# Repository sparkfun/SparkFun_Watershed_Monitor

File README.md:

# SparkFun Watershed Monitor

Repository Contents
-------------------

* **/Documentation** - Data sheets, additional product information
* **/Hardware** - Eagle design files (.brd, .sch)
* **/Production** - Production panel files (.brd)

License Information
-------------------

This product is _**open source**_! 

Please review the LICENSE.md file for license information. 

If you have any questions or concerns on licensing, please contact technical support on our [SparkFun forums](https://forum.sparkfun.com/viewforum.php?f=152).

Distributed as-is; no warranty is given.

- Your friends at SparkFun.

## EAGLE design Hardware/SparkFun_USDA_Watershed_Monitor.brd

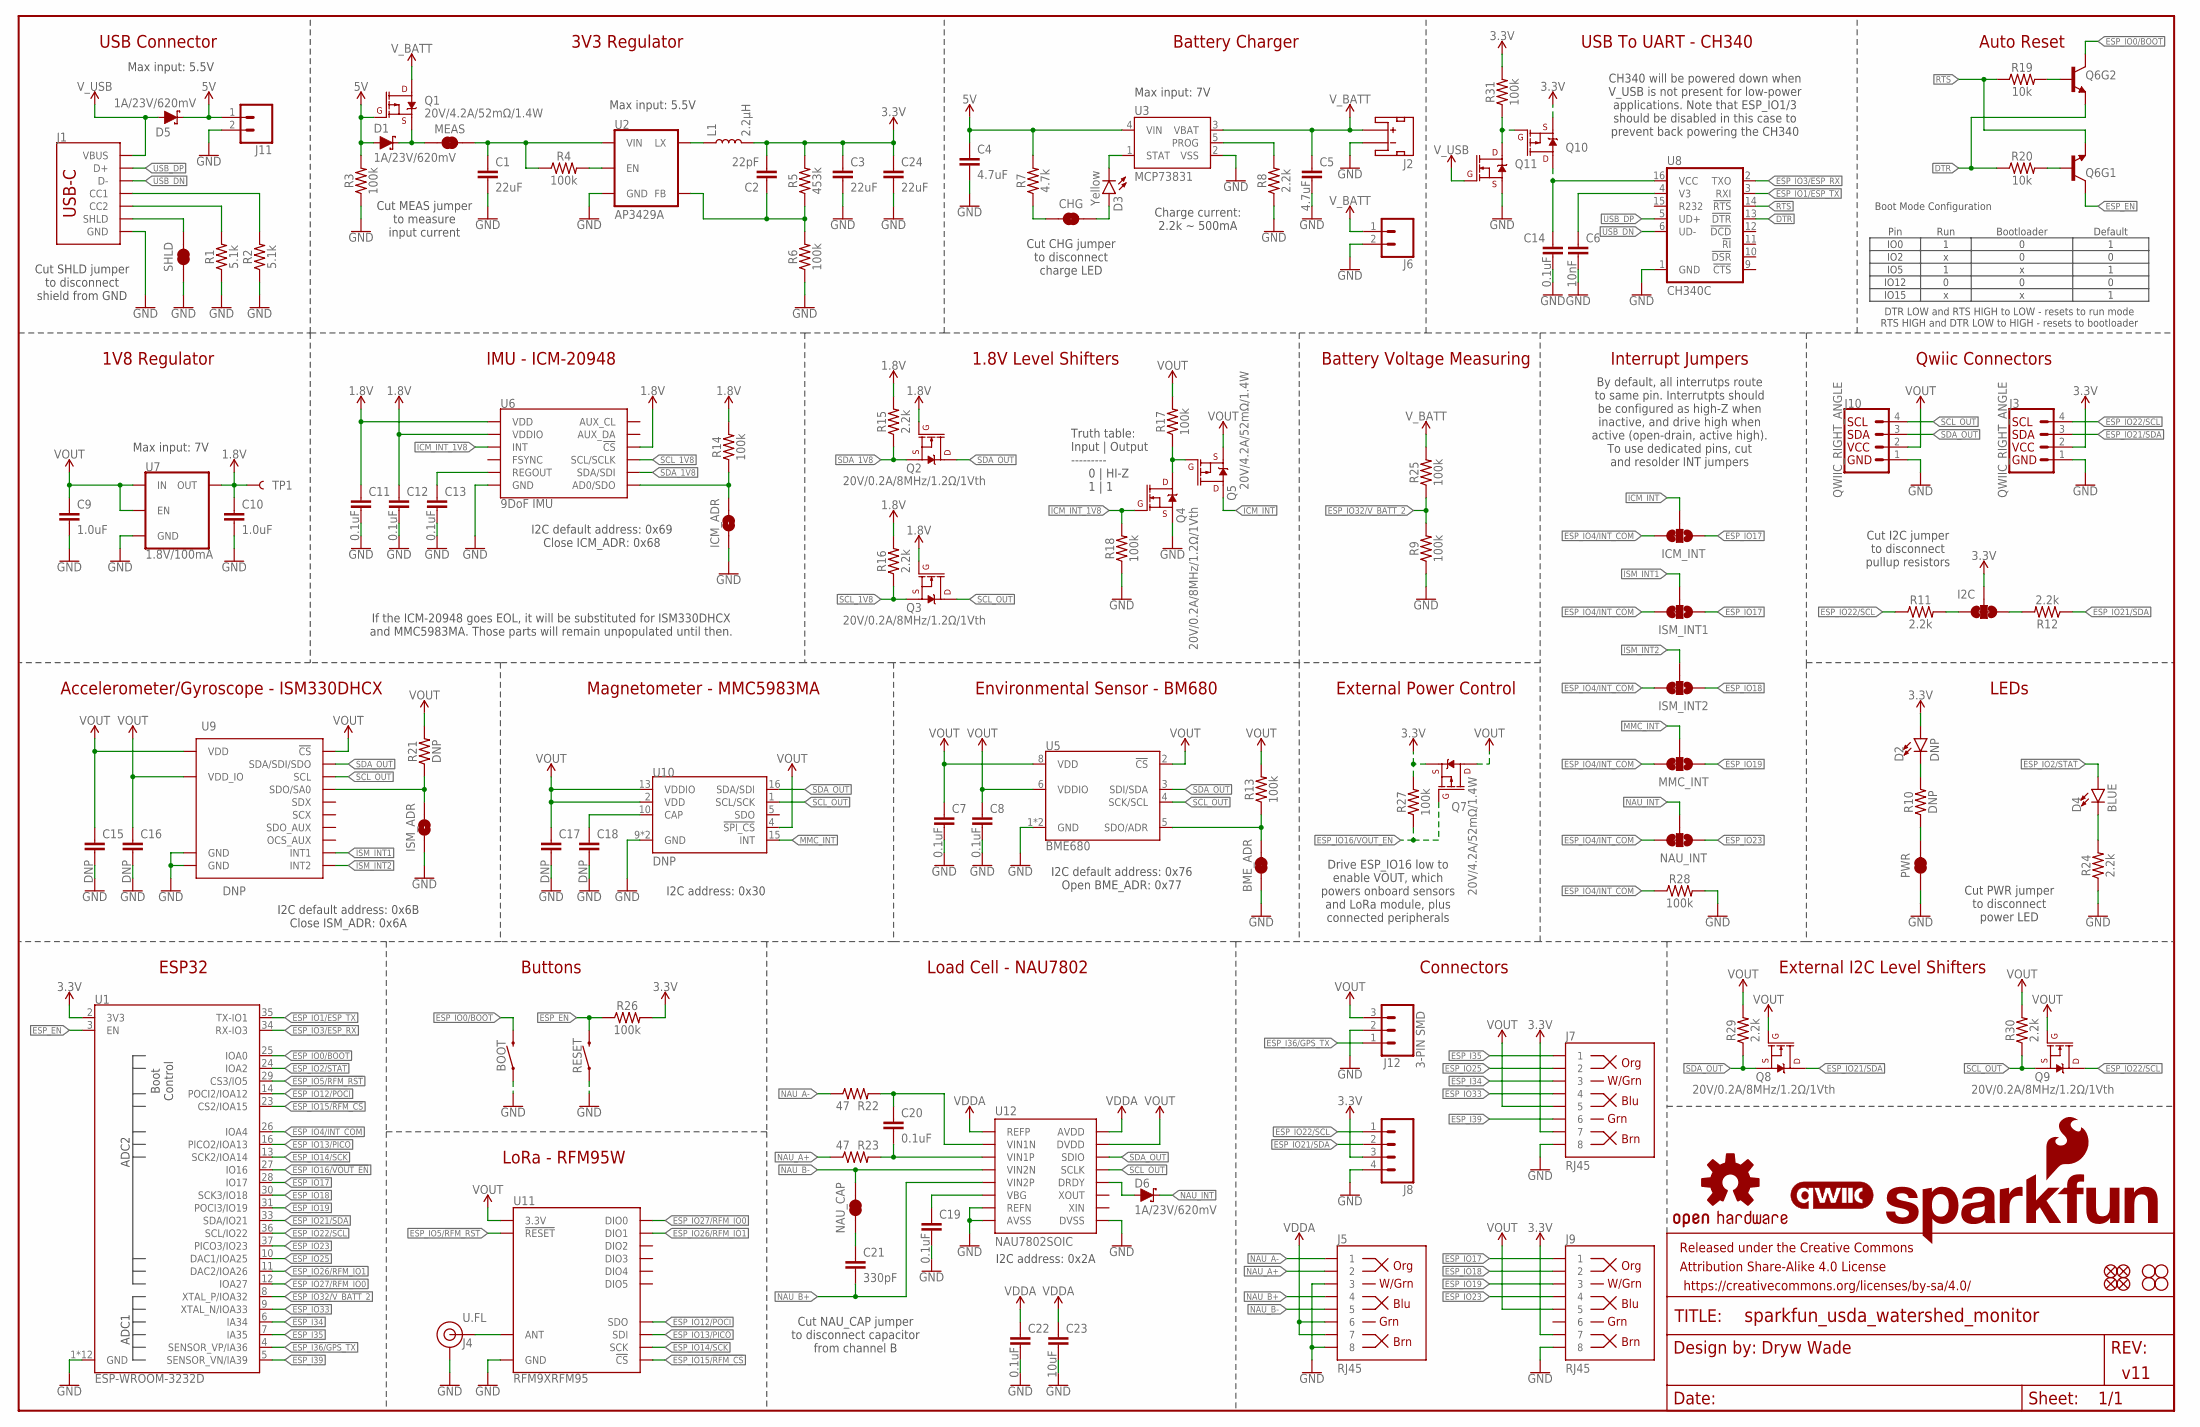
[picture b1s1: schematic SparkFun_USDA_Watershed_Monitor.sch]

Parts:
BME_ADR: JUMPER-SMT_2_NC_TRACE_SILK; SMT-JUMPER_2_NC_TRACE_SILK
BOOT: MOMENTARY-SWITCH-SPST-SMD-4.6X2.8MM; TACTILE_SWITCH_SMD_4.6X2.8MM
C1, C3, C24: 22uF; 0805
C2: 22pF; 0603
C4, C5: 4.7uF; 0603
C6: 10nF; 0603
C7, C8, C11, C12, C13, C14, C19, C20, C22: 0.1uF; 0603
C9, C10: 1.0uF; 0603
C15, C16, C17, C18: DNP; 0603
C21: 330pF; 0603
C23: 10uF; 0603
CHG: JUMPER-SMT_2_NC_TRACE_SILK; SMT-JUMPER_2_NC_TRACE_SILK
D1, D5, D6: 1A/23V/620mV; SOD-323
D2: DNP; LED-0603
D3: Yellow; LED-0603
D4: BLUE; LED-0603
FD1, FD2, FD3, FD4: FIDUCIAL1X2; FIDUCIAL-1X2
FRAME1: FRAME-LEDGER; CREATIVE_COMMONS
H1, H2, H3, H4: STAND-OFF
I2C: JUMPER-SMT_3_2-NC_TRACE_SILK; SMT-JUMPER_3_2-NC_TRACE_SILK
ICM_ADR: JUMPER-SMT_2_NO_SILK; SMT-JUMPER_2_NO_SILK
ICM_INT: JUMPER-SMT_3_1-NC_TRACE_SILK; SMT-JUMPER_3_1-NC_TRACE_SILK
ISM_ADR: JUMPER-SMT_2_NO_SILK; SMT-JUMPER_2_NO_SILK
ISM_INT1, ISM_INT2: JUMPER-SMT_3_1-NC_TRACE_SILK; SMT-JUMPER_3_1-NC_TRACE_SILK
J1: USB_C_2-LAYER_PADS; USB-C-16P-2LAYER-PADS
J2: JST_2MM_MALE; JST-2-SMD
J3, J10: QWIIC_RIGHT_ANGLE; JST04_1MM_RA
J4: U.FL
J5, J7, J9: RJ45; RJ45-8
J6, J11: CONN_021X02_NO_SILK; 1X02_NO_SILK
J8: CONN_041X04_NO_SILK_NO_POP; 1X04_NO_SILK
J12: 3-PIN SMD; JST-3-SMD
L1: 2.2μH; INDUCTOR_4X4MM
LOGO1: SFE_LOGO_NAME_FLAME.1_INCH; SFE_LOGO_NAME_FLAME_.1
LOGO2: OSHW-LOGOS; OSHW-LOGO-S
LOGO3: QWIIC_LOGO_4MM; QWIIC_4MM
MEAS: JUMPER-COMBO_2_NC_TRACE; COMBO-JUMPER_2_NC_TRACE
MMC_INT: JUMPER-SMT_3_1-NC_TRACE_SILK; SMT-JUMPER_3_1-NC_TRACE_SILK
NAU_CAP: JUMPER-SMT_2_NC_TRACE_SILK; SMT-JUMPER_2_NC_TRACE_SILK
NAU_INT: JUMPER-SMT_3_1-NC_TRACE_SILK; SMT-JUMPER_3_1-NC_TRACE_SILK
PWR: JUMPER-SMT_2_NC_TRACE_SILK; SMT-JUMPER_2_NC_TRACE_SILK
Q1, Q5, Q7, Q10: 20V/4.2A/52mΩ/1.4W; SOT23-3
Q2, Q3, Q4, Q8, Q9, Q11: 20V/0.2A/8MHz/1.2Ω/1Vth; SOT-416FL
Q6: TRANS_NPN_DUAL-MBT3904DW1T1; SC70-6
R1, R2: 5.1k; 0603
R3, R4, R6, R9, R13, R14, R17, R18, R25, R26, R27, R28, R31: 100k; 0603
R5: 453k; 0603
R7: 4.7k; 0603
R8, R11, R12, R15, R16, R24, R29, R30: 2.2k; 0603
R10, R21: DNP; 0603
R19, R20: 10k; 0603
R22, R23: 47; 0603
RESET: MOMENTARY-SWITCH-SPST-SMD-4.6X2.8MM; TACTILE_SWITCH_SMD_4.6X2.8MM
SHLD: JUMPER-SMT_2_NC_TRACE_SILK; SMT-JUMPER_2_NC_TRACE_SILK
TP1: TEST-POINT3X4; PAD.03X.04
U1: ESP-WROOM-3232D; ESP-WROOM-32D
U2: AP3429A; SOT23-5
U3: MCP73831; SOT23-5
U5: BME680; LGA3.0X3.0
U6: 9DoF IMU; QFN24-3X3-ICM-20948
U7: 1.8V/100mA; SC70
U8: CH340C; SO016
U9: DNP; LGA-14L
U10: DNP; LGA-16-3X3MM-4X4PINS
U11: RFM9XRFM95; RFM95
U12: NAU7802SOIC; SO16

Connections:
1.8V: C10.1, C11.1, C12.1, Q2.1 (G), Q3.1 (G), R14.2, R15.2, R16.2, TP1.1, U6.8 (VDDIO), U6.13 (VDD), U6.22 (!CS), U7.5 (OUT)
3.3V: C2.2, C3.1, C24.1, D2.A, I2C.2, J3.2, J7.7, J8.3, J9.7, L1.P$2 (2), Q7.2 (S), Q10.2 (S), R5.2, R26.2, R27.2, R31.2, U1.2 (3V3)
3V3_EN: R4.2, U2.1 (EN)
5V: C4.1, D1.A, D5.C, J11.1, Q1.1 (G), R3.2, R7.2, U3.4 (VIN)
DTR: Q6.1 (E), R20.1, U8.13 (!DTR)
ESP_EN: Q6.3 (C), R26.1, RESET.3 (2), RESET.4 (2), U1.3 (EN)
ESP_I34: J7.3, U1.6 (IA34)
ESP_I35: J7.1, U1.7 (IA35)
ESP_I36/GPS_TX: J12.1 (3), U1.4 (SENSOR_VP/IA36)
ESP_I39: J7.6, U1.5 (SENSOR_VN/IA39)
ESP_IO0/BOOT: BOOT.3 (2), BOOT.4 (2), Q6.6 (C), U1.25 (IOA0)
ESP_IO1/ESP_TX: U1.35 (TX-IO1), U8.3 (RXI)
ESP_IO2/STAT: D4.A, U1.24 (IOA2)
ESP_IO3/ESP_RX: U1.34 (RX-IO3), U8.2 (TXO)
ESP_IO4/INT_COM: ICM_INT.3, ISM_INT1.3, ISM_INT2.3, MMC_INT.3, NAU_INT.3, R28.1, U1.26 (IOA4)
ESP_IO5/!RFM_RST!: U1.29 (CS3/IO5), U11.!RESET
ESP_IO12/POCI: U1.14 (POCI2/IOA12), U11.SDO
ESP_IO13/PICO: U1.16 (PICO2/IOA13), U11.SDI
ESP_IO14/SCK: U1.13 (SCK2/IOA14), U11.SCK
ESP_IO15/!RFM_CS!: U1.23 (CS2/IOA15), U11.NSS (!CS!)
ESP_IO16/!VOUT_EN!: Q7.1 (G), R27.1, U1.27 (IO16)
ESP_IO17: ICM_INT.1, ISM_INT1.1, J9.1, U1.28 (IO17)
ESP_IO18: ISM_INT2.1, J9.2, U1.30 (SCK3/IO18)
ESP_IO19: J9.3, MMC_INT.1, U1.31 (POCI3/IO19)
ESP_IO21/SDA: J3.3, J8.2, Q8.3 (D), R12.1, U1.33 (SDA/IO21)
ESP_IO22/SCL: J3.4, J8.1, Q9.3 (D), R11.1, U1.36 (SCL/IO22)
ESP_IO23: J9.4, NAU_INT.1, U1.37 (PICO3/IO23)
ESP_IO25: J7.2, U1.10 (DAC1/IOA25)
ESP_IO26/RFM_IO1: U1.11 (DAC2/IOA26), U11.DIO1
ESP_IO27/RFM_IO0: U1.12 (IOA27), U11.DIO0
ESP_IO32/V_BATT_2: R9.2, R25.1, U1.8 (XTAL_P/IOA32)
ESP_IO33: J7.4, U1.9 (XTAL_N/IOA33)
GND: BME_ADR.1, BOOT.1, BOOT.2 (1), C1.2, C3.2, C4.2, C5.2, C6.2, C7.2, C8.2, C9.2, C10.2, C11.2, C12.2, C13.2, C14.2, C15.2, C16.2, C17.2, C18.2, C19.2, C22.2, C23.2, C24.2, ICM_ADR.1, ISM_ADR.1, J1.GND, J1.GND2 (GND), J2.1 (-), J3.1, J4.1 (GND), J4.2 (GND), J5.3, J5.8, J6.2, J7.8, J8.4, J9.8, J10.1, J11.2, J12.2, PWR.1, Q4.2 (S), Q11.2 (S), R1.1, R2.1, R3.1, R6.1, R8.1, R9.1, R18.1, R24.1, R28.2, RESET.1, RESET.2 (1), SHLD.1, U1.1 (GND), U1.15 (GND), U1.38 (GND), U1.GND, U1.GNDT1 (GND), U1.GNDT2 (GND), U1.GNDT3 (GND), U1.GNDT4 (GND), U1.GNDT5 (GND), U1.GNDT6 (GND), U1.GNDT7 (GND), U1.GNDT8 (GND), U2.2 (GND), U3.2 (VSS), U5.1 (GND), U5.7 (GND), U6.18 (GND), U6.20 (GND), U7.2 (GND), U8.1 (GND), U9.P6 (GND), U9.P7 (GND), U10.9 (GND), U10.11 (GND), U11.GND@1 (GND), U11.GND@2 (GND), U11.GND@3 (GND), U12.7 (REFN), U12.8 (AVSS), U12.9 (DVSS)
ICM_INT: ICM_INT.2, Q5.3 (D)
ICM_INT_1V8: Q4.1 (G), R18.2, U6.12 (INT)
ISM_INT1: ISM_INT1.2, U9.P4 (INT1)
ISM_INT2: ISM_INT2.2, U9.P9 (INT2)
MMC_INT: MMC_INT.2, U10.15 (INT)
unnamed: D4.C, R24.2
unnamed: L1.P$1 (1), U2.3 (LX)
unnamed: C1.1, MEAS.2, MEAS.4 (2), R4.1, U2.4 (VIN)
unnamed: J1.B5 (CC2), R1.2
unnamed: J1.A5 (CC1), R2.2
unnamed: D1.C, MEAS.1, MEAS.3 (1), Q1.2 (S)
unnamed: C2.1, R5.1, R6.2, U2.5 (FB)
unnamed: D3.C, U3.1 (STAT)
unnamed: CHG.2, D3.A
unnamed: CHG.1, R7.1
unnamed: R8.2, U3.5 (PROG)
unnamed: C6.1, U8.4 (V3)
unnamed: BME_ADR.2, R13.1, U5.5 (SDO/ADR)
unnamed: C13.1, U6.10 (REGOUT)
unnamed: I2C.1, R12.2
unnamed: I2C.3, R11.2
unnamed: ICM_ADR.2, R14.1, U6.9 (AD0/SDO)
unnamed: Q6.5 (B), R20.2
unnamed: Q6.2 (B), R19.2
unnamed: C18.1, U10.10 (CAP)
unnamed: ISM_ADR.2, R21.1, U9.P1 (SDO/SA0)
unnamed: C19.1, U12.6 (VBG)
unnamed: D2.C, R10.2
unnamed: C21.1, NAU_CAP.1
unnamed: J4.FEED (SIGNAL), U11.ANT
unnamed: PWR.2, R10.1
unnamed: C20.2, R23.2, U12.3 (VIN1P)
unnamed: C20.1, R22.2, U12.2 (VIN1N)
unnamed: D6.A, U12.12 (DRDY)
unnamed: Q4.3 (D), Q5.1 (G), R17.1
unnamed: Q10.1 (G), Q11.3 (D), R31.1
unnamed: C14.1, Q10.3 (D), U8.16 (VCC)
NAU_A+: J5.2, R23.1
NAU_A-: J5.1, R22.1
NAU_B+: C21.2, J5.4, U12.5 (VIN2P)
NAU_B-: J5.5, NAU_CAP.2, U12.4 (VIN2N)
NAU_INT: D6.C, NAU_INT.2
RTS: Q6.4 (E), R19.1, U8.14 (!RTS)
SCL_1V8: Q3.2 (S), R16.1, U6.23 (SCL/SCLK)
SCL_OUT: J10.4, Q3.3 (D), Q9.2 (S), R30.1, U5.4 (SCK/SCL), U9.P13 (SCL), U10.1 (SCL/SCK), U12.13 (SCLK)
SDA_1V8: Q2.2 (S), R15.1, U6.24 (SDA/SDI)
SDA_OUT: J10.3, Q2.3 (D), Q8.2 (S), R29.1, U5.3 (SDI/SDA), U9.P14 (SDA/SDI/SDO), U10.16 (SDA/SDI), U12.14 (SDIO)
SHLD: J1.SHLD1 (SHLD), J1.SHLD2 (SHLD), J1.SHLD3 (SHLD), J1.SHLD4 (SHLD), SHLD.2
USB_DN: J1.A7 (D-), J1.B7 (D-), U8.6 (UD-)
USB_DP: J1.A6 (D+), J1.B6 (D+), U8.5 (UD+)
VDDA: C22.1, C23.1, J5.6, J5.7, U12.1 (REFP), U12.16 (AVDD)
VOUT: C7.1, C8.1, C9.1, C15.1, C16.1, C17.1, J7.5, J9.5, J10.2, J12.3 (1), Q5.2 (S), Q7.3 (D), Q8.1 (G), Q9.1 (G), R13.2, R17.2, R21.2, R29.2, R30.2, U5.2 (!CS), U5.6 (VDDIO), U5.8 (VDD), U7.1 (IN), U7.3 (EN), U9.P5 (VDD_IO), U9.P8 (VDD), U9.P12 (!CS!), U10.2 (VDD), U10.4 (!SPI_CS!), U10.13 (VDDIO), U11.3.3V, U12.15 (DVDD)
V_BATT: C5.1, J2.2 (+), J6.1, Q1.3 (D), R25.2, U3.3 (VBAT)
V_USB: D5.A, J1.VBUS1 (VBUS), J1.VBUS2 (VBUS), Q11.1 (G)

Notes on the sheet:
Dryw Wade
v11
USB Connector
3V3 Regulator
Battery Charger
LEDs
Qwiic Connectors
Environmental Sensor - BM680
1V8 Regulator
IMU - ICM-20948
1.8V Level Shifters
Cut SHLD jumper to disconnect shield from GND
Cut MEAS jumper to measure input current
Cut CHG jumper to disconnect charge LED
Charge current: 2.2k ~ 500mA
Cut PWR jumper to disconnect power LED
Cut I2C jumper to disconnect pullup resistors
I2C default address: 0x69 Close ICM_ADR: 0x68
By default, all interrutps route to same pin. Interrutpts should be configured as high-Z when inactive, and drive high when active (open-drain, active high). To use dedicated pins, cut and resolder INT jumpers
Interrupt Jumpers
USB To UART - CH340
Accelerometer/Gyroscope - ISM330DHCX
Magnetometer - MMC5983MA
LoRa - RFM95W
Load Cell - NAU7802
ESP32
Cut NAU_CAP jumper to disconnect capacitor from channel B
Buttons
Auto Reset
Connectors
Battery Voltage Measuring
Max input: 5.5V
If the ICM-20948 goes EOL, it will be substituted for ISM330DHCX and MMC5983MA. Those parts will remain unpopulated until then.
I2C default address: 0x6B Close ISM_ADR: 0x6A
I2C default address: 0x76 Open BME_ADR: 0x77
I2C address: 0x2A
Max input: 7V
DTR LOW and RTS HIGH to LOW - resets to run mode RTS HIGH and DTR LOW to HIGH - resets to bootloader
Pin
IO0

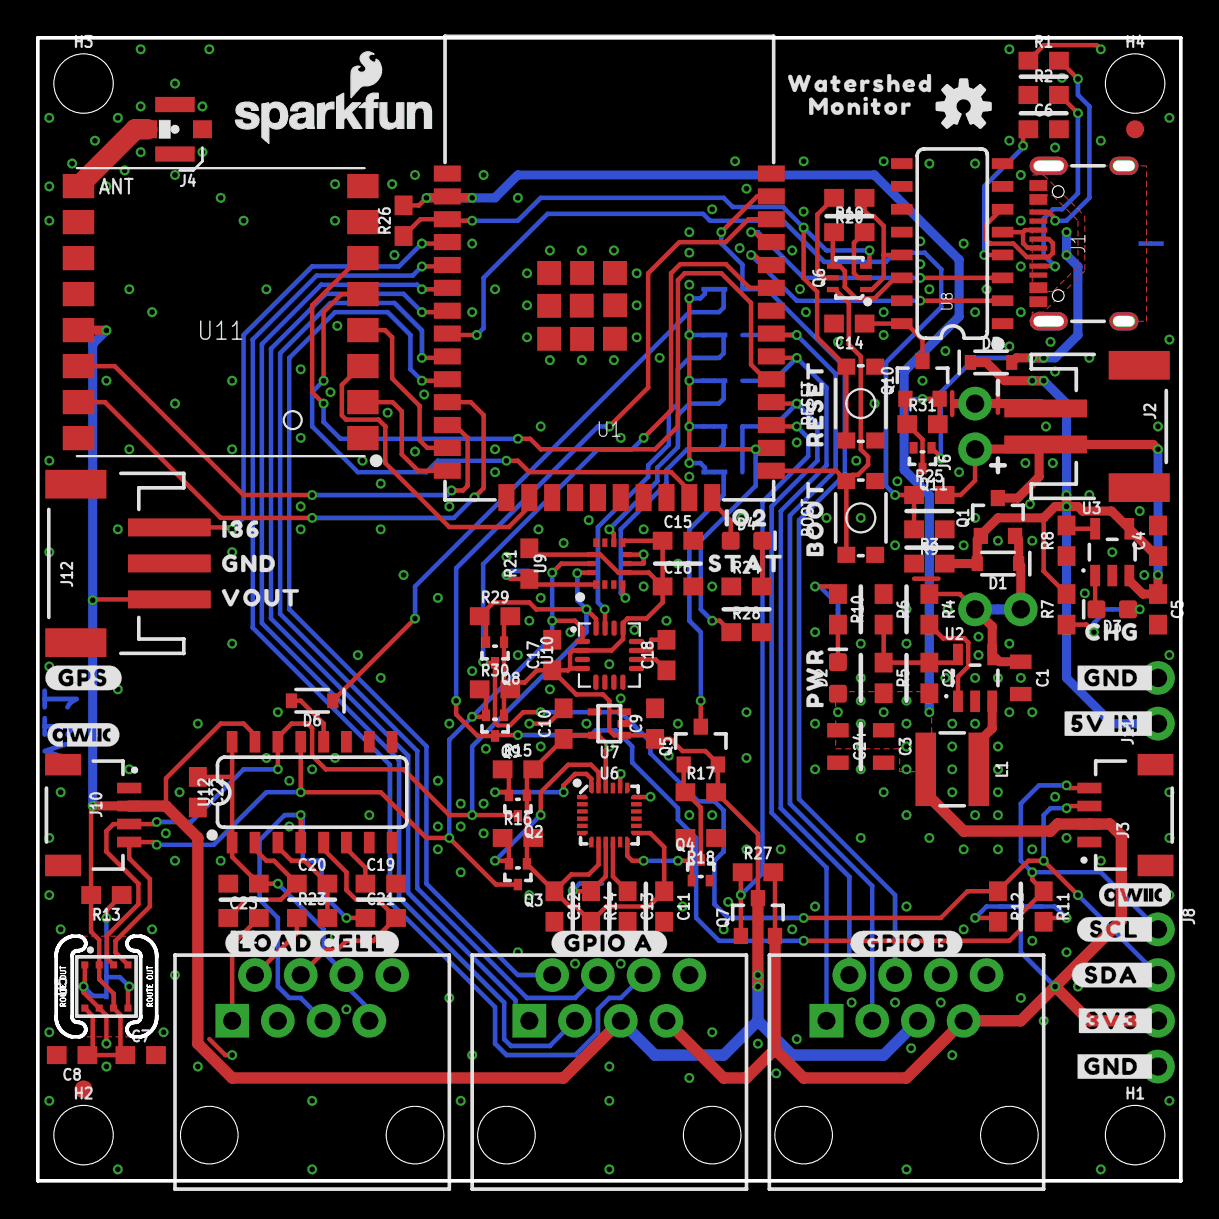
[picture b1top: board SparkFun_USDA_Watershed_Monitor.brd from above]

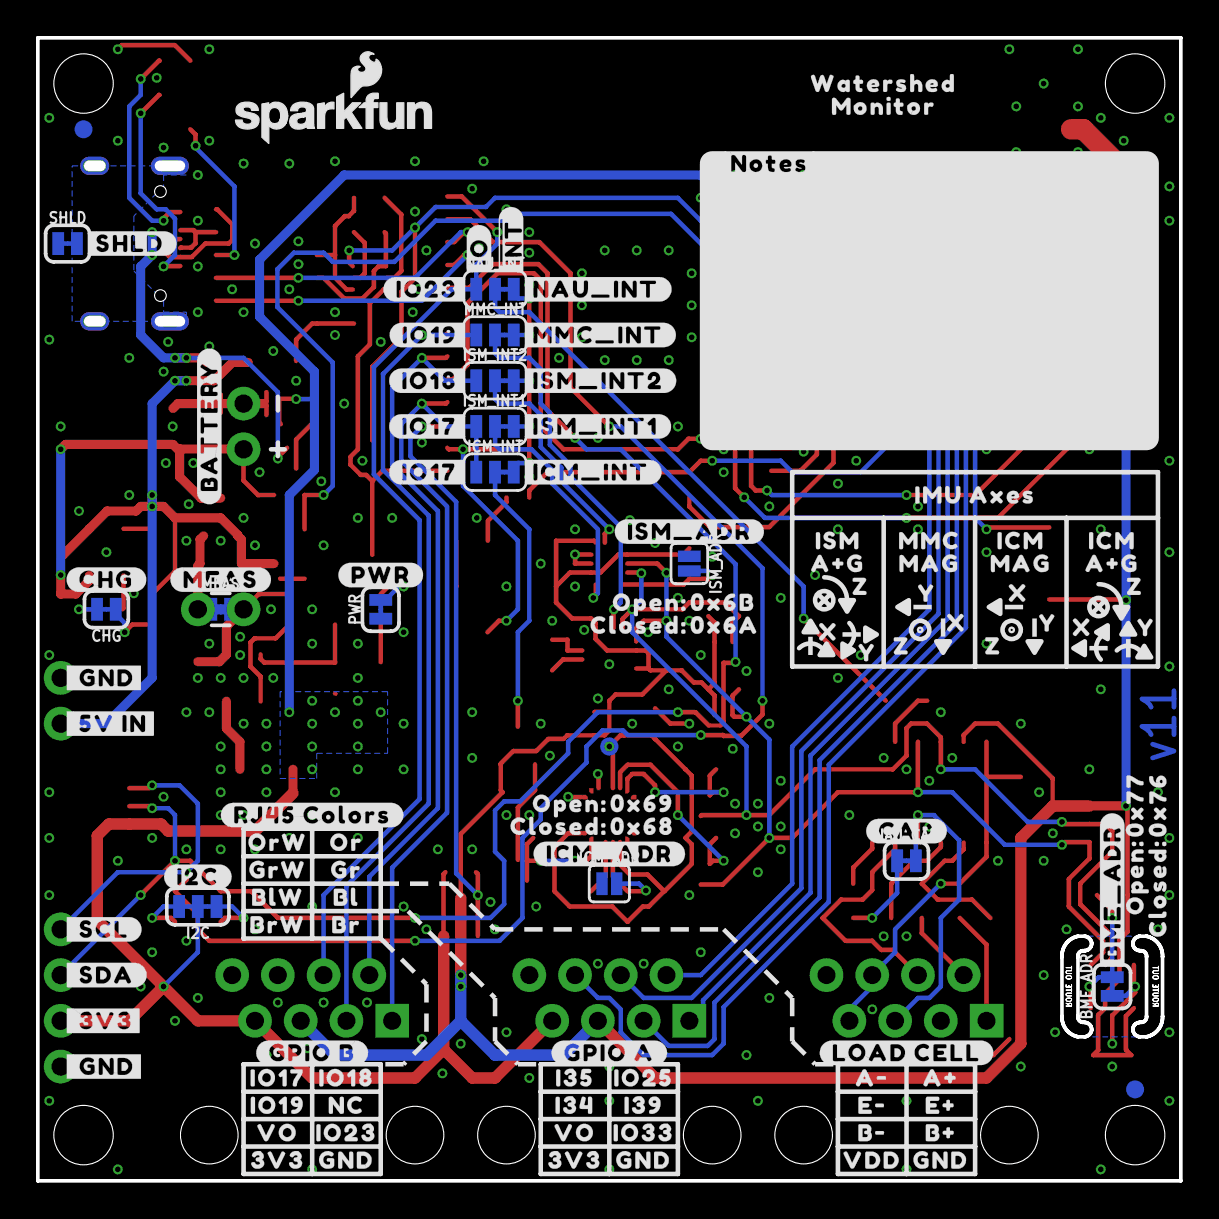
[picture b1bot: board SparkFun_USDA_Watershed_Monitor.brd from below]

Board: 2 copper layers, 63.5 x 63.5 mm, 249 parts (118 on the bottom side), 87 nets.

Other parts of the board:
LOGO4: QWIIC_LOGO_4MM; QWIIC_4MM
LOGO5: SFE_LOGO_NAME_FLAME.1_INCH; SFE_LOGO_NAME_FLAME_.1
U$2, U$115: WATERSHED0
U$3, U$116: MONITOR0
U$4, U$8, U$11: GND0
U$5, U$67: #IO17#0
U$6, U$79: #GND_#0
U$7, U$80: #_GND#0
U$9: #MEAS#0
U$10, U$24: 3V30
U$12: A#0
U$13: VDD0
U$14: #CHG#0
U$15: #I2C#0
U$16: CHG0
U$17: #CAP#0
U$18: #BME_ADR#0
U$19: #ICM_ADR#0
U$20: #ISM_ADR#0
U$21: #BATTERY#0
U$22: #SHLD#0
U$23: I360
U$25, U$69: VO0
U$26: VOUT0
U$27: RESET0
U$28: BOOT0
U$29: PWR0
U$30: STAT0
U$31: IO20
U$32: ORW0
U$33: OR0
U$34: GRW0
U$35: GR0
U$36: BLW0
U$37: BL0
U$38: BRW0
U$39: BR0
U$40: A#1
U$41: B#0
U$42: B#1
U$43: E#0
U$44: E#1
U$45: #RJ45_COLORS#0
U$46: #PWR#0
U$47: #3V3_#0
U$48: #SDA_#0
U$49: ORDERING_INSTRUCTIONS
U$50, U$55: #LOAD_CELL#0
U$51, U$86: #GPIO_A#0
U$52: IO250
U$53, U$87: #GPIO_B#0
U$54: IO330
U$56: #SCL_#0
U$57: NC0
U$58: IO170
U$59: IO180
U$60: IO190
U$61: I340
U$62: I350
U$64: I390
U$65: #IO19#0
U$66: #IO18#0
U$68: #IO23#0
U$70: #NAU_INT#0
U$71: #MMC_INT#0
U$72: #ISM_INT2#0
U$73: #ISM_INT1#0
U$74: #ICM_INT#0
U$75: #IO#0
U$76: ##INT##0
U$77: #NOTES#0
U$78: IO230
U$81: #_SCL#1
U$82, U$121, U$125: OPEN#0
U$83, U$122, U$126: CLOSED#0
U$84: #_SDA#2
U$85: #_3V3#0
U$88: #GPS#0
U$89: GND3
U$94, U$100, U$104, U$138: X0
U$95, U$102, U$105, U$139: Y0
U$96, U$103, U$106, U$140: Z0
U$110, U$137: ICM0
U$111: ISM0
U$112: MMC0
U$113: IMU_AXES0
U$117: #5V_IN_#0
U$118: #_5V_IN#0
U$119: 0X770
U$120: 0X760
U$123: 0X6A0
U$124: 0X6B0
U$127: 0X690
U$128: 0X680
U$141, U$142: MAG0
U$143, U$144: A#G0

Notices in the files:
parts and their libraries:
SparkFun-Aesthetics: Licensing: Creative Commons ShareAlike 4.0 International - https://creativecommons.org/licenses/by-sa/4.0
SparkFun-Aesthetics: Released under the Creative Commons Attribution Share-Alike 4.0 License
SparkFun-Aesthetics: https://creativecommons.org/licenses/by-sa/4.0
